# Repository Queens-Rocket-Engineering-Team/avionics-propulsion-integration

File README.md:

# Propulsion Integration Control Boards (Upper, Lower)
> 2025-2026 Season - Propulsion Integration Projects

-  Branch contains both board's **firmware**, **schematics**, and related **documentation and datasheets**.

### Folder Structure
- [`/Schematics`](./Schematics/) : PCB design files (KiCad V8)  
- [`/Firmware`](./Firmware/) : Arduino C/C++ code (to ESP32) for sensors, CAN/TWAI, and WiFi telemetry  
- [`/Datasheets`](./Datasheets/) : Datasheets and reference materials  
- [`.gitignore`](./.gitignore) : Build and temporary files excluded

---

**Branch created by:** Jeevan Sanchez

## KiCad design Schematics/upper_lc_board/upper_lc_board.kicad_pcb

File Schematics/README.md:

# LC Board Schematics

This directory contains PCB and schematic files for both LC boards (Kicad v8.0.6). 

Including:

- power managment for the ESP32 and board.
- MCU breakout circuitry, valve control, sensing circuits, communication.
- board layout and component placement.

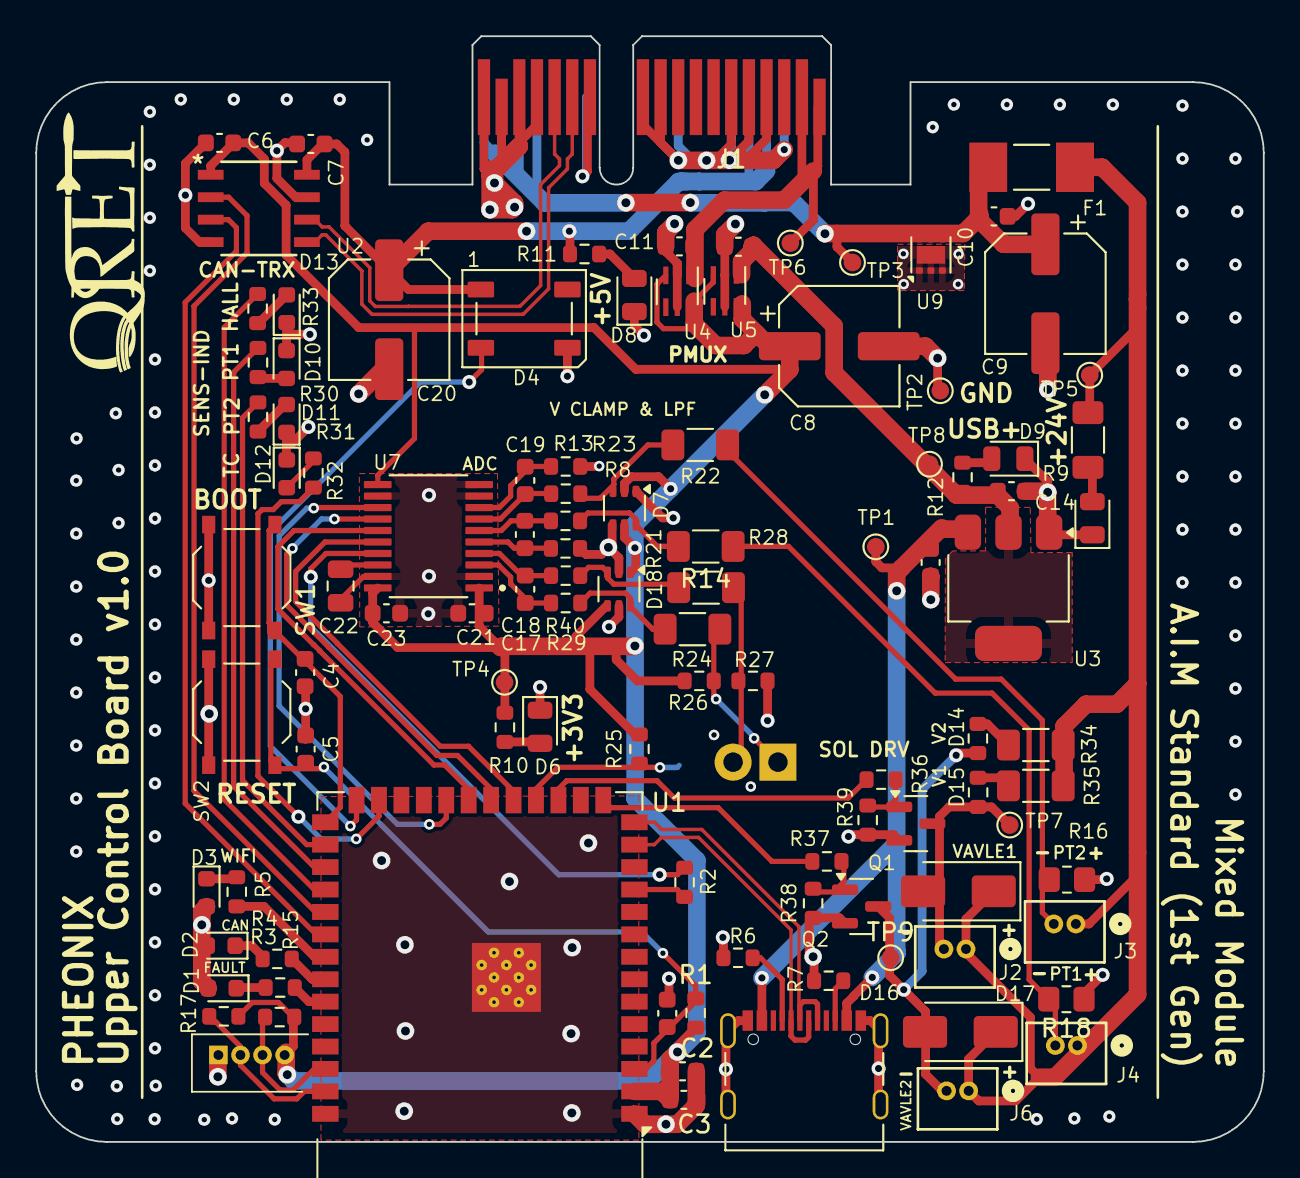
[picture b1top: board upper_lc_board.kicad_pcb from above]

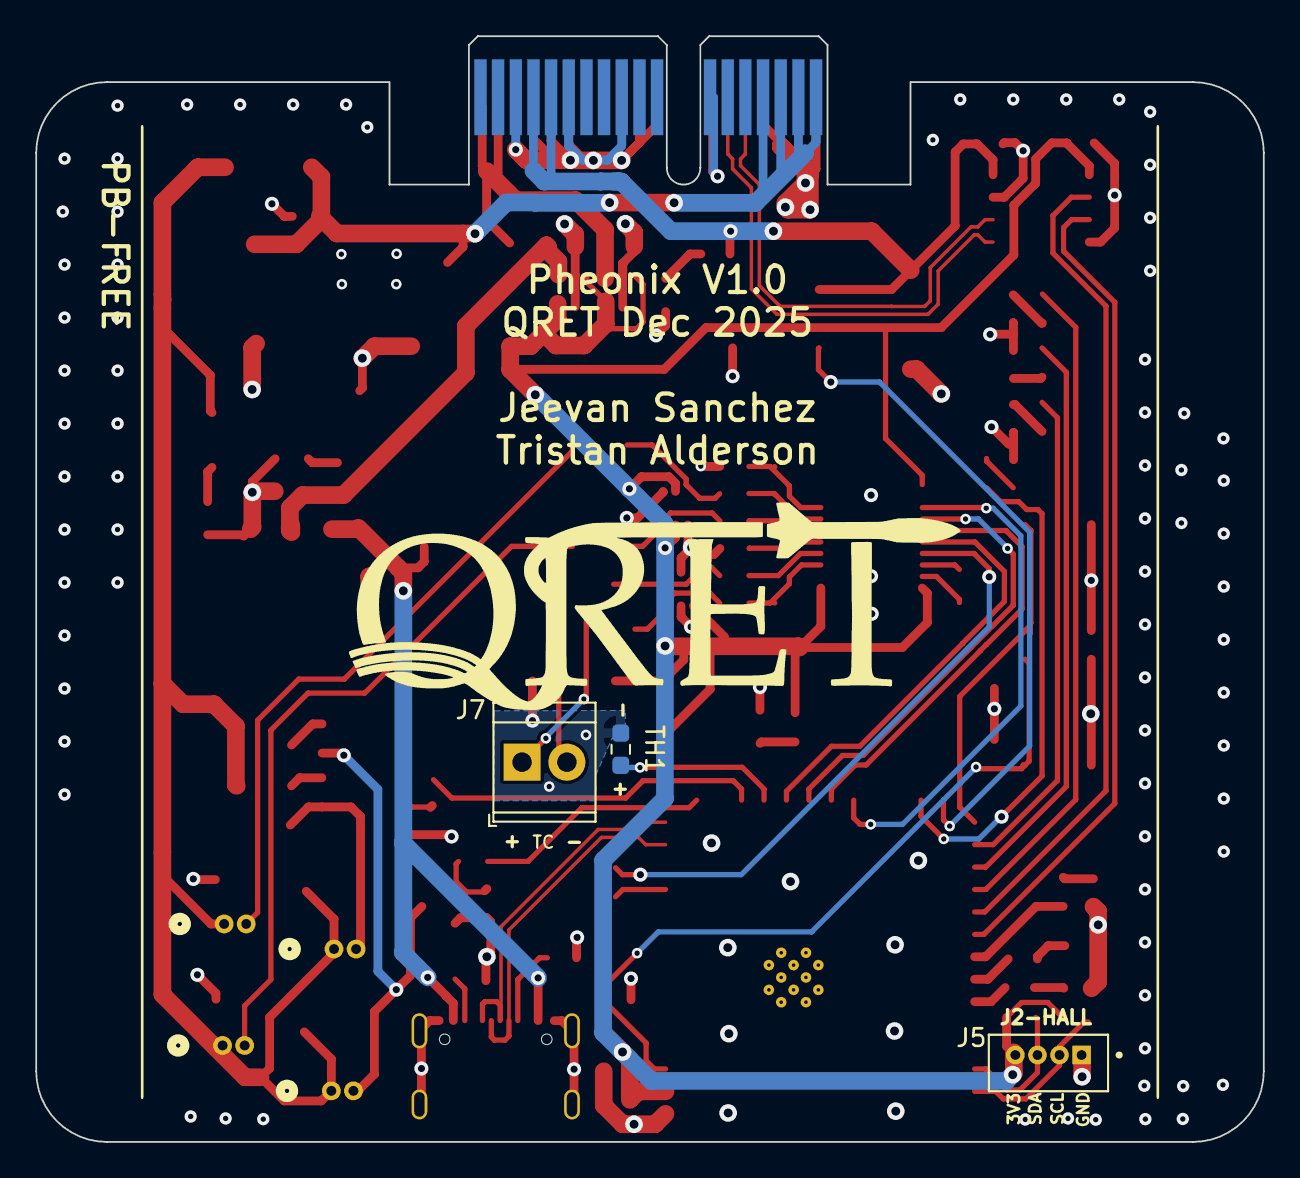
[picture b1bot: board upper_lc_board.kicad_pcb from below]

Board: 4 copper layers, 69.5 x 62.6 mm, 107 parts (3 on the bottom side), 69 nets.

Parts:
C1, C11, C12, C21, C23: 1uF; C_0603_1608Metric
C2, C4, C5, C6, C7, C10: 0.1uF; C_0603_1608Metric
C3, C13, C14: 10uF; C_0603_1608Metric
C8, C20: 100uF_16V; CP_Elec_6.3x5.9
C9: 100uF_35V; CP_Elec_6.3x5.9
C17, C18, C19: 10nF; C_0603_1608Metric
C22: 220 nF; C_0805_2012Metric
D1: FAULT_LED; LED_0603_1608Metric
D2: CAN_LED; LED_0603_1608Metric
D3: WIFI_LED; LED_0603_1608Metric
D4: SYS_LED_WS2812B; LED_WS2812B_PLCC4_5.0x5.0mm_P3.2mm
D5: PWR_24V_LED (GRN); LED_0805_2012Metric
D6: PWR_3V3_LED (GRN); LED_0805_2012Metric
D7, D18: BAV199DW; SOT-363_SC-70-6
D8: PWR_5V_LED (GRN); LED_0805_2012Metric
D9: USB_LED (GRN); LED_0805_2012Metric
D10, D11, D12, D13: LED; LED_0603_1608Metric
D14: SOL2_LED (YELW); R_0603_1608Metric
D15: SOL1_LED (YELW); R_0603_1608Metric
D16, D17: SS34; D_SMA
F1: Fuse; FUSC6125X279N
J1: Stack Male Edge Connector; BUS_PCIexpress_x1
J2: SOL1_CONN; CONN02_530470260_MOL
J3, J4: PT1; CONN02_530470260_MOL
J5: HALL; MOLEX_53047-0460
J6: SOL2_CONN; CONN02_530470260_MOL
J7: Screw_Terminal_01x02; TerminalBlock_TE_282834-2_1x02_P2.54mm_Horizontal
J8: USB_C_Female_USB2_Small; USB_C_DB-108PWB
Q1, Q2: AO3400A; SOT-23
R1, R25: 10k; R_0603_1608Metric
R2: 33; R_0603_1608Metric
R3, R4, R5, R10, R12, R30, R31, R32, R33: 150; R_0603_1608Metric
R6, R7: 5.1k; R_0603_1608Metric
R8, R13, R29, R36, R37, R40: 200; R_0603_1608Metric
R9, R34, R35: 4.7k; R_1206_3216Metric_Pad1.30x1.75mm_HandSolder
R11: 510; R_0603_1608Metric
R14, R22, R24, R28: 1k; R_1206_3216Metric_Pad1.30x1.75mm_HandSolder
R15, R17: 2.2k; R_0603_1608Metric
R16, R18: 165; R_0805_2012Metric_Pad1.20x1.40mm_HandSolder
R21, R23: 1.2k; R_0603_1608Metric
R26, R27: 1M; R_0603_1608Metric
R38, R39: 100k; R_0603_1608Metric
SW1: SW_ESP_BOOT_MODE; SW_Push_1P1T_XKB_TS-1187A
SW2: SW_ESP_RESET; SW_Push_1P1T_XKB_TS-1187A
TH1: Thermistor; R_0603_1608Metric_Pad0.98x0.95mm_HandSolder
TP1: 5V_USB; TestPoint_Pad_D1.0mm
TP2: GND; TestPoint_Pad_D1.0mm
TP3: 24V_BP; TestPoint_Pad_D1.0mm
TP4: 3V3; TestPoint_Pad_D1.0mm
TP5: 24V; TestPoint_Pad_D1.0mm
TP6: 3V3_BP; TestPoint_Pad_D1.0mm
TP7: VALVE1_OUT_TP; TestPoint_Pad_D1.0mm
TP8: 3V3_USB; TestPoint_Pad_D1.0mm
TP9: VALVE2_OUT_TP; TestPoint_Pad_D1.0mm
U1: ESP32-S3-WROOM-1-N16; ESP32-S3-WROOM-1
U2: ISO1044BDR; SOIC_1044BDR_TEX
U3: AMS1117-3.3; SOT-223-3_TabPin2
U4, U5: ID_LM66100DCKR; SC-70-6
U7: ADC_ADS131M04IPWR; SOP65P640X120-20N
U9: TVS3300DRV; WSON-6-1EP_2x2mm_P0.65mm_EP1x1.6mm

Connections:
5V_USB: C13.1, J8.A4 (VBUS), J8.A9 (VBUS), J8.B4 (VBUS), J8.B9 (VBUS), TP1.1, U3.3 (VI)
+3V3: C2.1, C3.1, C6.1, C8.1, C21.2, C23.2, D7.2 (K2), D7.5 (K4), D18.1 (A1), D18.4 (A3), J5.4, R1.1, R10.2, R15.2, R17.1, R25.2, R26.1, TP4.1, U1.2 (3V3), U2.1 (VCC1), U4.3 (*CE), U4.6 (VOUT), U5.3 (*CE), U5.6 (VOUT), U7.1 (AVDD), U7.11 (~SYNC/~RESET), U7.20 (DVDD)
+5V: C7.1, C20.1, D4.1 (VDD), J1.A4 (5.0V_A), J1.A5 (5.0V_A), R11.2, U2.8 (VCC2)
+24V: D16.1 (K), D17.1 (K), F1.1, J2.1, J3.1, J4.1, J6.1, R9.2, R34.2, R35.2, TP5.1
+24V_BP: C9.1, C10.1, F1.2, J1.A15 (24V_C), J1.A16 (24V_C), J1.A17 (24V_C), J1.A18 (24V_C), TP3.1, U9.4 (IN), U9.5 (IN), U9.6 (IN)
/ESP Breakout Cirucitry/ESP32_EN: C1.1, C5.2, R1.2, SW2.2, U1.3 (EN)
/ESP Breakout Cirucitry/ESP32_IO0: C4.2, SW1.2, U1.27 (IO0)
/ESP Breakout Cirucitry/GPIO_18: R2.1, U1.11 (IO18)
/ESP Breakout Cirucitry/GPIO_38: U1.31 (IO38), U2.2 (TXD)
/ESP Breakout Cirucitry/GPIO_39: U1.32 (IO39), U2.3 (RXD)
/ESP Breakout Cirucitry/GPIO_40: R5.1, U1.33 (IO40)
/ESP Breakout Cirucitry/GPIO_41: R4.1, U1.34 (IO41)
/ESP Breakout Cirucitry/GPIO_42: R3.1, U1.35 (IO42)
/ESP Breakout Cirucitry/GPIO_45: D4.2 (DOUT), U1.26 (IO45)
/ESP Breakout Cirucitry/USB_N: J8.A7 (D-), J8.B7 (D-), U1.13 (USB_D-)
/ESP Breakout Cirucitry/USB_P: J8.A6 (D+), J8.B6 (D+), U1.14 (USB_D+)
/Power Circuitry/3V3_BP: C11.2, J1.A1 (3.3V_A), J1.A2 (3.3V_A), TP6.1, U4.1 (VIN)
/Power Circuitry/3V3_USB: C12.1, C14.1, R12.1, TP8.1, U3.2 (VO), U5.1 (VIN)
/Sensor Circuitry/PT1: J4.2, R14.1, R18.2
/Sensor Circuitry/PT1_CLAMPED: C18.2, R13.1, U7.6 (AIN1P)
/Sensor Circuitry/PT2: J3.2, R16.2, R22.1
/Sensor Circuitry/PT2_CLAMPED: C19.2, R8.1, U7.7 (AIN2P)
/Sensor Circuitry/TC_N: J7.2, R27.1, R28.2
/Sensor Circuitry/TC_N_CLAMPED: C17.1, R40.2, U7.4 (AIN0N)
/Sensor Circuitry/TC_P: J7.1, R24.2, R26.2
/Sensor Circuitry/TC_P_CLAMPED: C17.2, R29.2, U7.3 (AIN0P)
ADC_CLKIN: R2.2, U7.17 (CLKIN)
ADC_DREADY: U1.22 (IO14), U7.13 (~DRDY)
ADC_MISO: U1.21 (IO13), U7.15 (DOUT)
ADC_MOSI: U1.19 (IO11), U7.16 (DIN)
ADC_SCLK: U1.20 (IO12), U7.14 (SCLK)
CAN_+: J1.B14 (CAN_H), U2.6 (CANH)
CAN_-: J1.B13 (CAN_L), U2.5 (CANL)
GND: C1.2, C2.2, C3.2, C4.1, C5.1, C6.2, C7.2, C8.2, C9.2, C10.2, C11.1, C12.2, C13.2, C14.2, C20.2, C21.1, C22.2, C23.1, D1.2 (A), D2.2 (A), D3.2 (A), D4.3 (VSS), D5.1 (K), D6.1 (K), D7.1 (A1), D7.4 (A3), D8.1 (K), D9.1 (K), D10.1 (K), D11.1 (K), D12.1 (K), D13.1 (K), D18.2 (K2), D18.5 (K4), J1.A3 (GND_A), J1.A6 (GND_A), J1.A9 (GND_B), J1.A12 (GND_B), J1.B4 (GND_A), J1.B5 (GND_A), J1.B6 (GND_A), J1.B10 (GND_B), J1.B11 (GND_B), J1.B12 (GND_B), J1.B15 (GND_C), J1.B16 (GND_C), J1.B17 (GND_C), J1.B18 (GND_C), J5.1, J8.A1 (GND), J8.A12 (GND), J8.B1 (GND), J8.B12 (GND), J8.S1 (SHIELD), Q1.2 (S), Q2.2 (S), R6.2, R7.2, R16.1, R18.1, R21.1, R23.1, R27.2, R38.1, R39.1, SW1.1, SW2.1, TH1.2, TP2.1, U1.1 (GND), U1.40 (GND), U1.41 (GND), U2.4 (GND1), U2.7 (GND2), U3.1 (GND), U4.2 (GND), U4.5 (ST), U5.2 (GND), U5.5 (ST), U7.2 (AGND), U7.9 (AIN3N), U7.10 (AIN3P), U7.12 (~CS), U7.19 (DGND), U9.1 (GND), U9.2 (GND), U9.3 (GND), U9.7 (GND)
HALL_LED: R33.1, U1.30 (IO37)
HALL_SCL: J5.2, R17.2, U1.39 (IO1)
HALL_SDA: J5.3, R15.1, U1.38 (IO2)
unnamed: D1.1 (K), R3.2
unnamed: D2.1 (K), R4.2
unnamed: D3.1 (K), R5.2
unnamed: D5.2 (A), R9.1
unnamed: D6.2 (A), R10.1
unnamed: D7.6 (K3A4), R13.2, R14.2
unnamed: D7.3 (K1A2), R8.2, R22.2
unnamed: D8.2 (A), R11.1
unnamed: D9.2 (A), R12.2
unnamed: D10.2 (A), R30.2
unnamed: D11.2 (A), R31.2
unnamed: D12.2 (A), R32.2
unnamed: D13.2 (A), R33.2
unnamed: D14.2 (A), R34.1
unnamed: D15.2 (A), R35.1
unnamed: D18.6 (K3A4), R24.1, R29.1
unnamed: D18.3 (K1A2), R28.1, R40.1
unnamed: J8.A5 (CC1), R6.1
unnamed: J8.B5 (CC2), R7.1
unnamed: Q1.1 (G), R36.1, R39.2
unnamed: Q2.1 (G), R37.1, R38.2
unnamed: C18.1, R21.2, U7.5 (AIN1N)
unnamed: C19.1, R23.2, U7.8 (AIN2N)
unnamed: C22.1, U7.18 (CAP)
PT1_LED: R30.1, U1.29 (IO36)
PT2_LED: R31.1, U1.28 (IO35)
SOL1_RET: D15.1 (K), D16.2 (A), J2.2, Q1.3 (D), TP7.1
SOL2_RET: D14.1 (K), D17.2 (A), J6.2, Q2.3 (D), TP9.1
TC_LED: R32.1, U1.25 (IO48)
TEMP_SENSE: R25.1, TH1.1, U1.18 (IO10)
VALVE1_CTRL: R36.2, U1.17 (IO9)
VALVE2_CTRL: R37.2, U1.15 (IO3)

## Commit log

2025-03-18 Fixed power LED voltage sources
    5V and 12V LEDs were connected to 3.3V. Thanks Teighin :)
2025-03-20 Changed to higher-performance sensors
    Changed main sensors to pin-compatible versions with higher performance:
    - Changed MS5607 to MS5611
    - Changed QMA6100P to KX134ACR
    No PCB changed are required.
2025-06-12 Quick tx/rx firmware pair
2025-06-12 Flash debug LED, removed blocking delays
2025-06-12 Lowered canbus baud rate to 62.5kHz
2025-06-12 Set USB pins to NC pins; we in debug-by-LED land rn
2025-06-12 Compiled binary files on a known-good system
2025-10-10 init base repo for LC board
2025-10-10 add readme and template
2025-10-10 add subfolder-specific readme
2025-10-23 add esp32 datasheet, start considering ultrasonic models next
2025-10-23 add documentation
2025-10-23 Enhance README with more documentation details
    Updated README to include additional documentation notes.
2025-10-29 add more datasheets, PCB files (main, breakout)
2025-10-29 rewrites
2025-10-29 Rename ESP32_breakout.kicad_sch to ESP_breakout.kicad_sch
2025-10-29 Rename ESP32_breakout.kicad_pcb to ESP_breakout.kicad_pcb
2025-11-05 breakout circuitry complete, added datasheets
2025-11-07 update breakout circuitry (check documentation on notion), power module.
2025-11-13 add power module with ORing circuit, add datasheets on each symbol.
2025-11-13 update power module
2025-11-15 start sensor module
2025-11-19 update power circuitry with new backplane symbol
2025-11-21 finish sensor circuitry & add sensor documentation to notion.
2025-11-21 restructure file structure, start solenoid driver circuitry
2025-11-22 start solenoid driver circuitry
2025-11-22 add solenoid driver circuitry
2025-11-22 SSR replacement for solenoid driver
2025-11-23 add hiearchical sheets in main board file
2025-11-24 global symbols/component annotations fix
2025-11-24 start PCB file, start assigning footprints, omit fuse, JST conns for now, still assigning resistors and some diodes
2025-11-24 start layout, finish assigning footprints. TODO -> verify ESP32 pinout, continue layout
2025-11-24 layout update; still need to add small components (caps, resistors), and add silkscreen
2025-11-25 small
2025-11-25 v control
2025-11-25 continue
2025-11-25 update board, add new fuse
2025-11-25 add new adc to schematic
2025-11-25 update board with new ADC & crystal
2025-11-25 start revising main layout for accessibility
2025-11-26 update layout with new connector
2025-11-27 quick commit for ADC circuitry updates
2025-11-27 2nd temp commit for new ADC circuitry
2025-11-27 start redesigning ADC circuitry, organize schematic files. adding OPAMPS for buffered voltage divider on HALL & on PTs. layout to be adjusted after.
2025-11-27 update sensor circuitry; implement reccomended pre-ADC circuitry
2025-12-01 update power circuitry (replaced OR-ing setup with a single power mux IC)
2025-12-01 solenoid schematic review, reveiewing sensors and ESP-breakout next, then finalizing layout
2025-12-02 reviewing schematics
2025-12-02 finish power circuitry (MUX)
2025-12-02 breakout circuitry review
2025-12-04 add TC circuitry; finish layout next.
2025-12-05 temp commit for layout work
2025-12-06 update schematic & board with smaller diode footprints
2025-12-06 fix footprint designators
2025-12-06 layout work, implement ADC low pass filter layout next
2025-12-06 add filter components to layout
2025-12-06 revise & organize some circuitry, next: replace MUX with ideal diodes, finish layout, rename GPIO labels for clarity
2025-12-07 more layout work, add FAULT LED
    next: revert to ideal diode circuitry instead of MUX IC.
2025-12-08 add vertical connectors, revert MUX circuitry to ORing setup w ideal diodes
2025-12-08 finish adding components to layout, revise layout next.
2025-12-09 temp commit for CJC alternative change
2025-12-10 add thermistor circuitry & update layout
2025-12-10 small layout revisions
2025-12-10 add testing points throughout board schematic
2025-12-11 fix button footprint issue
2025-12-12 fix shunt resistor, add test point to layout
    - sync issue with backplane connector footprint
2025-12-14 start routing
    - routing done for solenoids, power, and some other sub-circuits.
2025-12-15 route ADC circuitry, some more sensor & misc. routing
    -> low pass filter routing was a pain
2025-12-17 routing work
2025-12-18 more routing work
    USB routing
2025-12-19 local changes
2025-12-19 Revert "Init commit of cleaned up hybrid power module"
    This reverts commit 1ed412c4767fa7241b6af34ec0461c7642127650.
2025-12-19 Init commit of cleaned up hybrid power module
2025-12-19 fixed/updated CAN transceiver
2025-12-20 add new CAN, 4-pin conn for hall sensor, general routing work.
    #TODO - clear design rules check
2025-12-21 add silkscreen, gnd pour, vias
2025-12-21 remove ground pour for review
2025-12-22 Updated all gpio for better routing, > - removed diode array, and 5v sensing > - added dedicated clk generator for adc
2025-12-23 added serial comm support and automatic flashing via uart bridge
2025-12-24 fixed pin naming convention and updated gpios for better routing
2025-12-24 finalized pcb traces and part placement
2025-12-24 small update to adc ground plane and touch point placement
2025-12-24 silkscreen
2025-12-24 more silkscreen
2025-12-24 switching to primarily 0603 footprints and started adding LSCS numbers
2025-12-26 added most part number (LCSC, Digikey), verified current limiting resitors
2025-12-27 slight schematic naming changes, some comment cleanup
2025-12-28 final pcb routing and part numbers
2025-12-28 fix failed merge, fix part number issues
2025-12-28 cleanup thermocouple routing, add ground pour for thermistor
2025-12-29 clean up silkscreen and routing
2025-12-29 fixed incorrect footprints and part numbers
2025-12-29 updated opamp, 24v tvs diode, and excluded usbc antenna overlap error
2025-12-29 fixed valve FB diode footprints, fixed major silkscreen warnings
2026-01-01 updates after review using screw terminal for TC removed opamps for clamping diodes fixed solenoid FB diodes manual solder large SMDs on edges
2026-01-06 clean up schematics
2026-01-06 organize footprint, models, and datasheets folders
2026-01-06 add hierarchy sheet blocks for valve, TC & PT circuitry.
    confirmed that nets are consistent with layout, no problems.
2026-01-06 fix merge issue
2026-01-06 fixed
2026-01-06 matched pcb silk to fabricated one
2026-01-06 update READMES
2026-01-08 add relative datasheets to symbol fields
2026-01-08 update PCB with fields
2026-01-08 remove old symbol files
2026-01-08 add references to caps, ferrite bead footprint, LDO datasheet
2026-01-09 init commit for allowing shared schematics accross kicad projects
2026-01-09 add rest of files to support sharing
2026-01-09 fixed TC, PT, Valve schematic references and confirmed by updating PCB
2026-01-09 add decoupling, revise power circuitry (ferrite bead, LDO swap), merge shared-schemtic branch changes.
